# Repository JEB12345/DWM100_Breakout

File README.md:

# DWM100_Breakout
A Breakout board to mount a DWM1000 module onto SUPERball's XBee WiFi slot on the Sensor Board

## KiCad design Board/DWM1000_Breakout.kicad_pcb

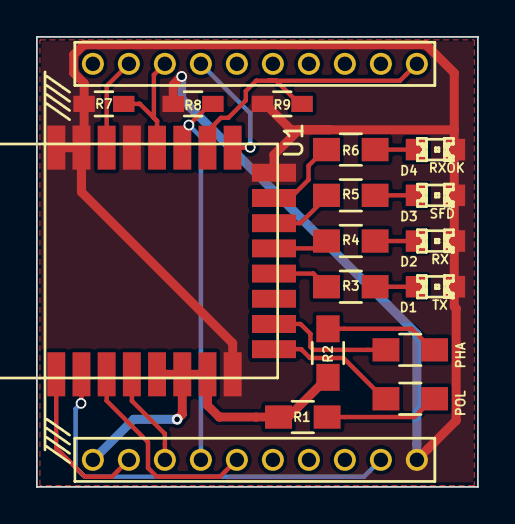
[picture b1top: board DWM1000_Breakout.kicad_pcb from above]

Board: 2 copper layers, 24.5 x 25.0 mm, 18 parts (0 on the bottom side), 23 nets.

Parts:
D1, D2, D3, D4: LED; LED-0805
JP1, JP2: Jumper_NO_Small; R_0805_HandSoldering
P1, P2: CONN_01X10; xbee_2mm_pinheader_1x10
R1, R2: 1K; R_0805_HandSoldering
R3, R4, R5, R6: 470; R_0805_HandSoldering
R7, R8, R9: 0; R_0603_HandSoldering
U1: DWM1000; dmw1000

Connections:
+3V3: P1.1, R1.2, R2.2, U1.5, U1.6, U1.7
/CLK: P2.3, R7.2, U1.20
/EXTON: P1.2, U1.1
/IRQ: P2.2, U1.22
/MISO: P1.4, R8.2, U1.19
/MOSI: P2.10, R9.2, U1.18
/RESET: P1.5, U1.3
/RXLED: R4.2, U1.13
/RXOKLED: R6.2, U1.15
/SFDLED: R5.2, U1.14
/SPIPHA: JP2.2, U1.10
/SPIPOL: JP1.2, U1.9
/SYNC: P1.3, U1.4
/TXLED: R3.2, U1.12
/WAKEUP: P1.9, U1.2
/nSELECT: P2.4, U1.17
GND: D1.1, D2.1, D3.1, D4.1, P1.10, R7.1, R8.1, R9.1, U1.8, U1.16, U1.21, U1.23, U1.24
unnamed: D1.2, R3.1
unnamed: D2.2, R4.1
unnamed: D3.2, R5.1
unnamed: D4.2, R6.1
unnamed: JP1.1, R1.1
unnamed: JP2.1, R2.1

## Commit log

2015-06-03 Added a gitignore file
2015-06-03 Added gerbers for the board. However, I deleted all the original files...
2015-06-03 Updated gitignore to ignore zip files `
2015-06-04 Rebuilt the whole project after initial git fail
2015-06-04 updated the README.md
